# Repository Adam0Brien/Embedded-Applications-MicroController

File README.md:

# Embedded-Applications-MicroController
Microcontroller project for 2nd Year IoT &amp; WIT
---------------------------------------------------

<p1>Hello World working on the lcd Screen</p1>

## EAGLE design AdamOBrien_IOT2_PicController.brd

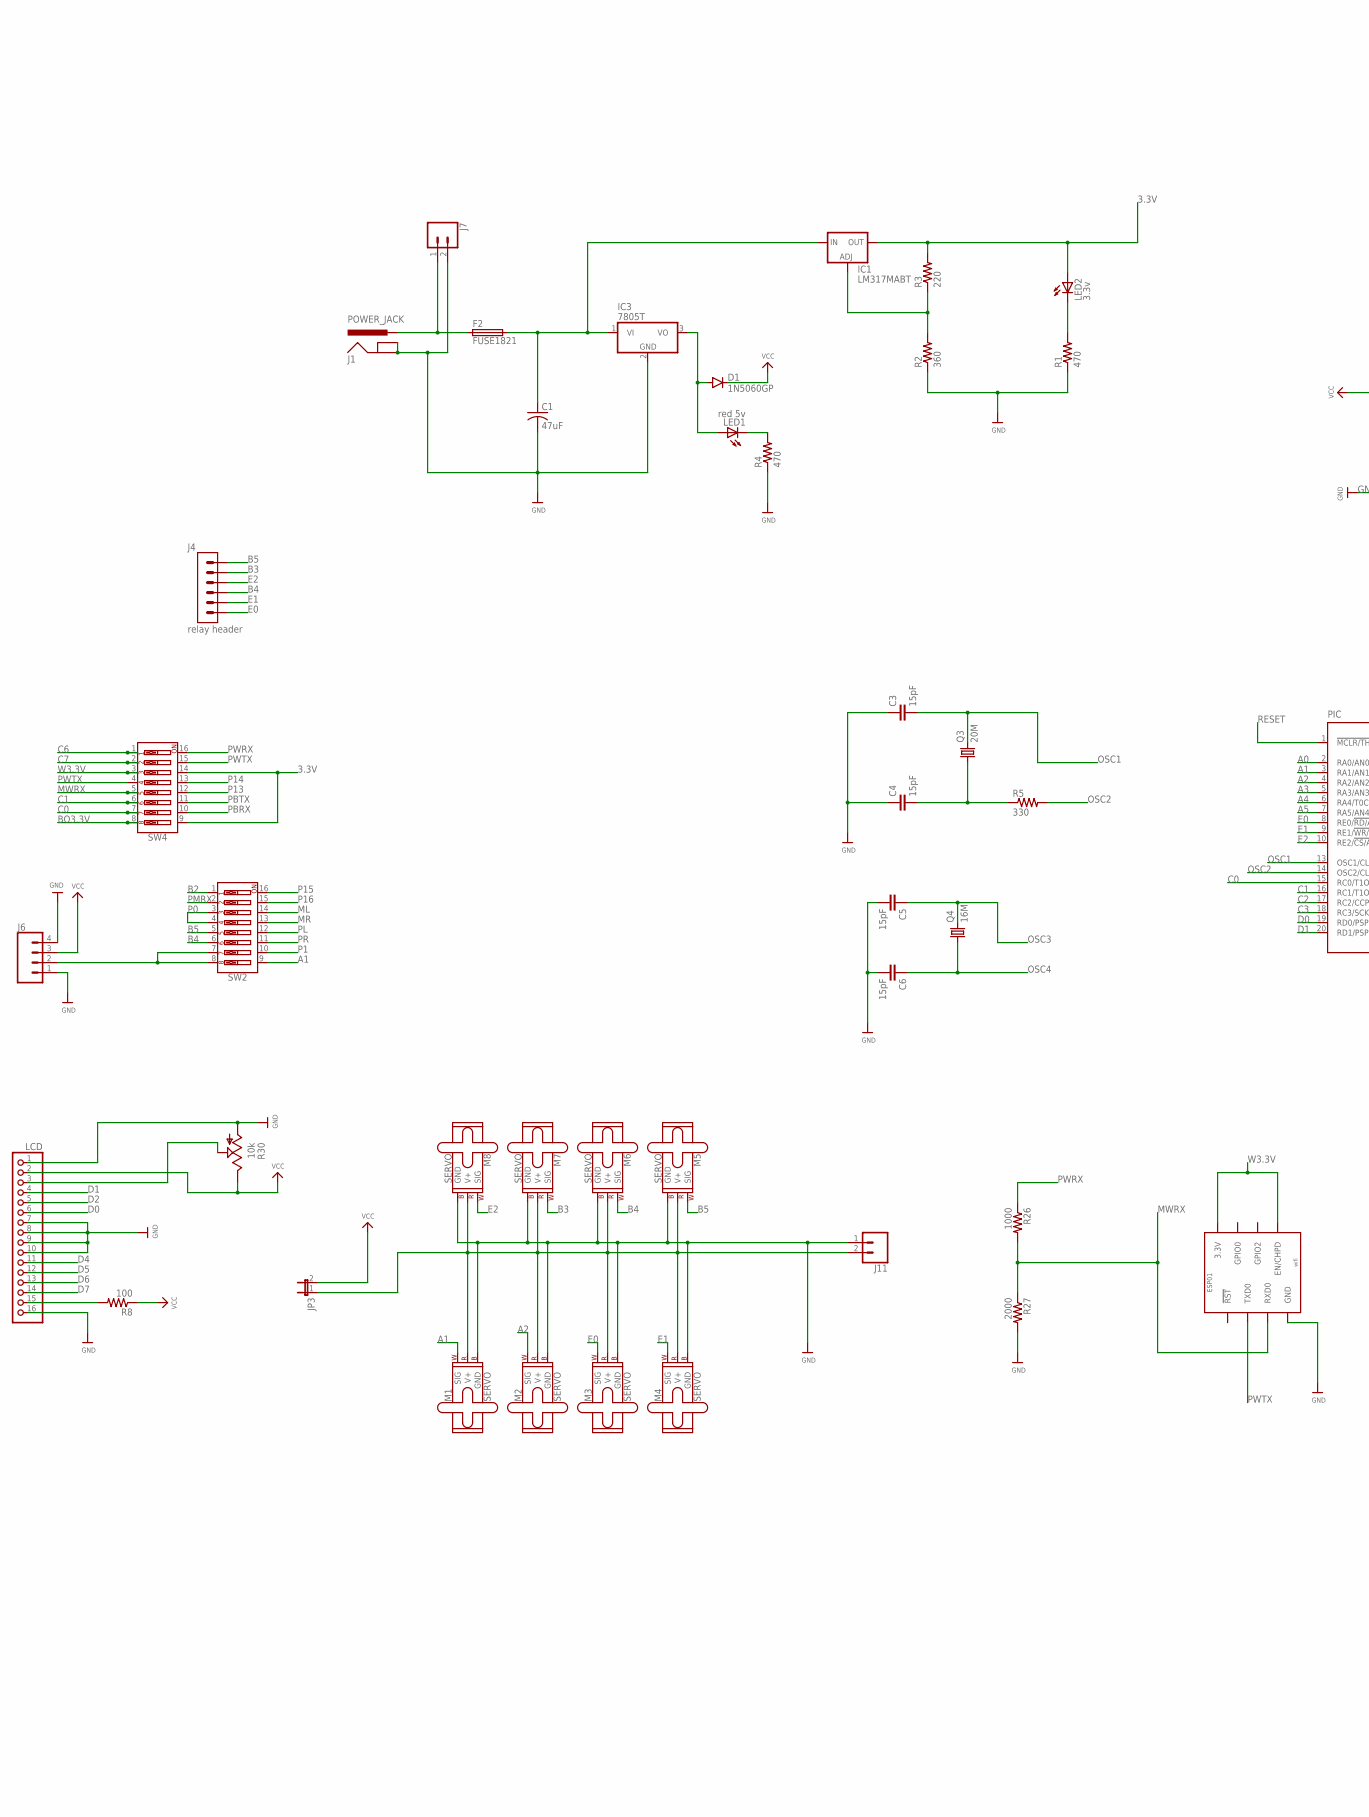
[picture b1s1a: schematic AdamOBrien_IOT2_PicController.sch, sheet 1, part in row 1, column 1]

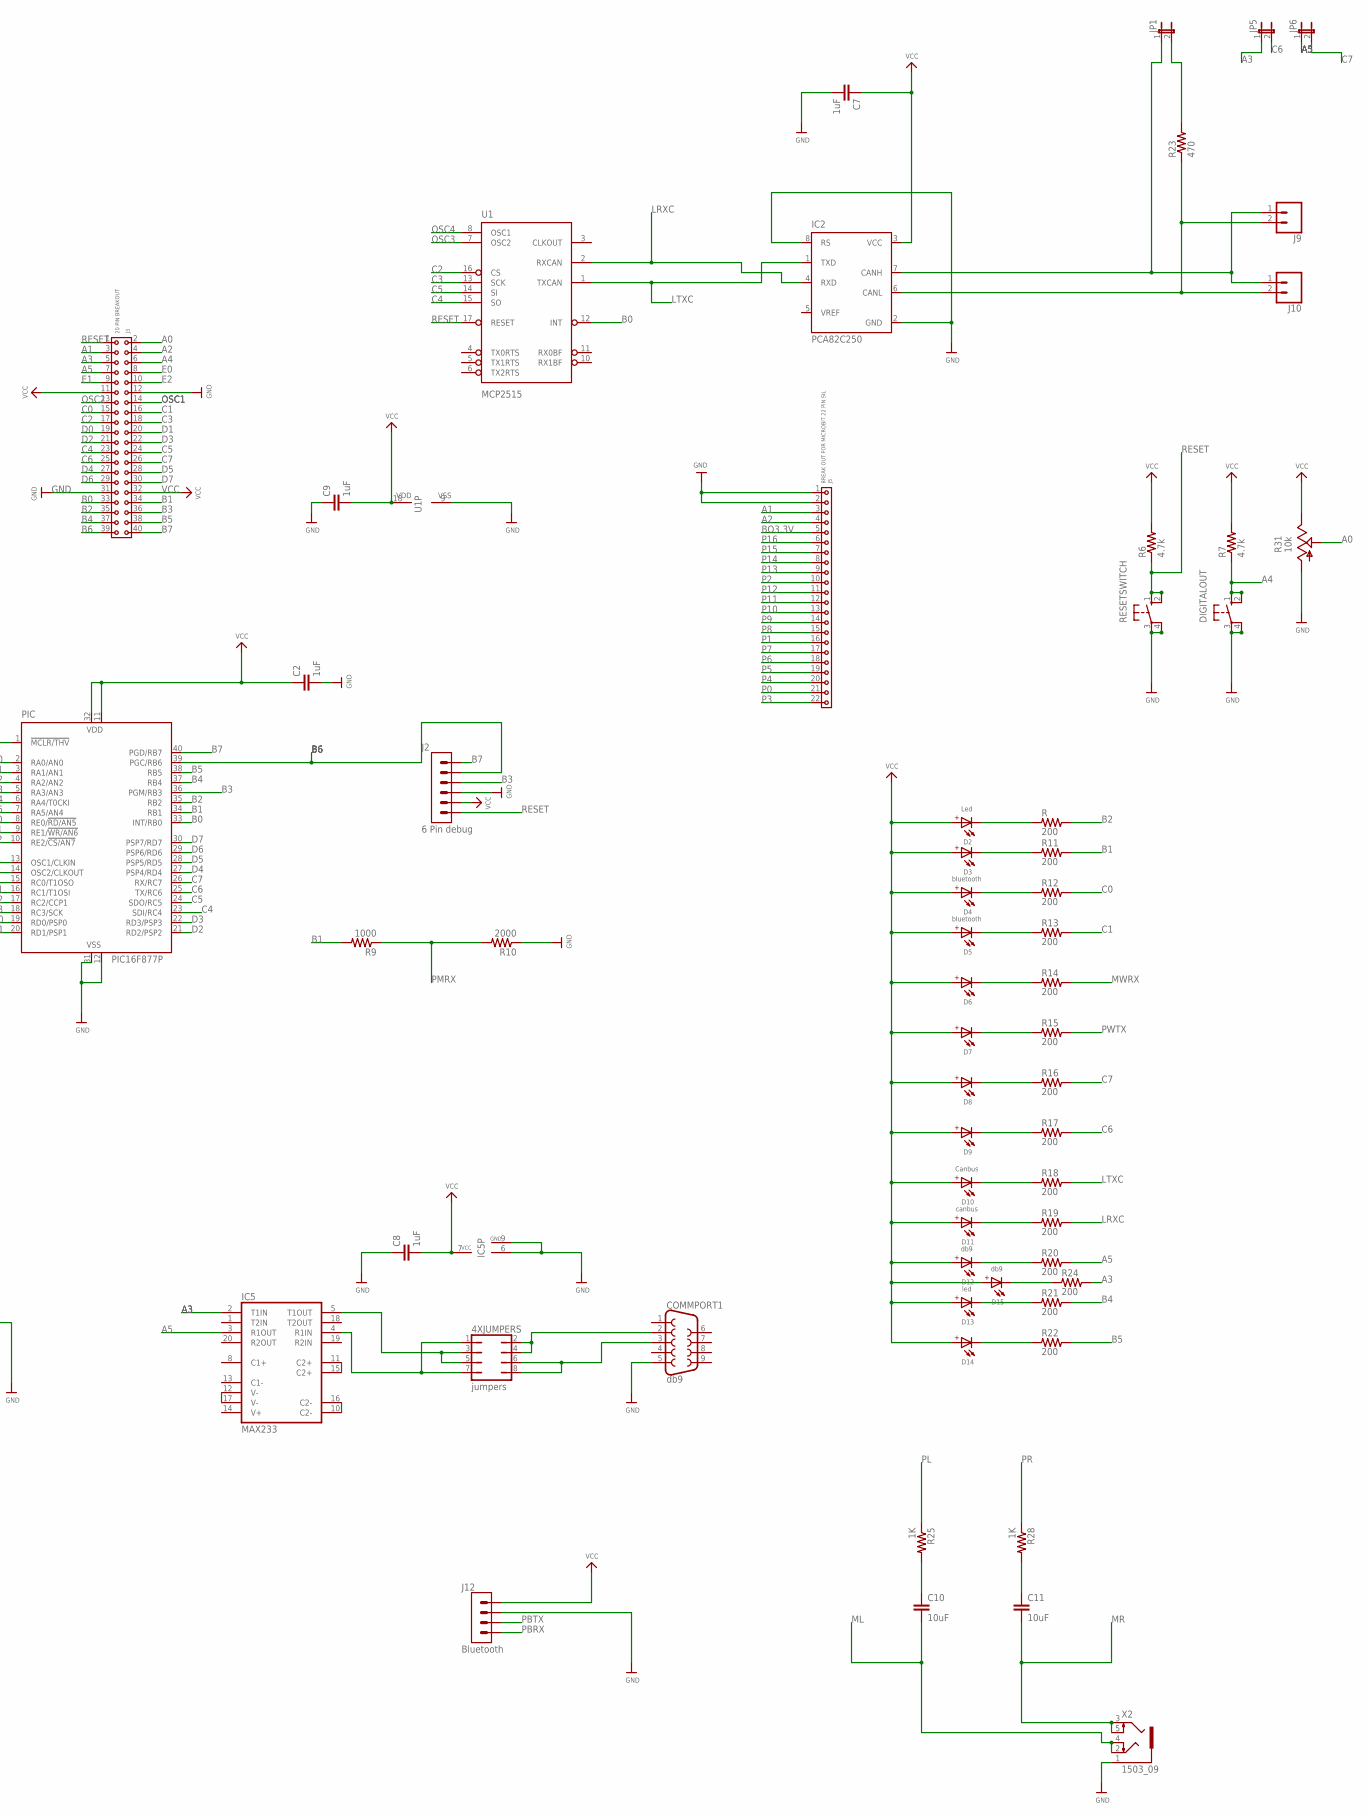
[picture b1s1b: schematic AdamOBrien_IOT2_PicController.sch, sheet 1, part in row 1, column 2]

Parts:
4XJUMPERS: jumpers; JP4Q
C1: 47uF; C025-024X044
C2, C7, C8, C9: 1uF; C2.5-2
C3, C4, C5, C6: 15pF; C2.5-2
C10, C11: 10uF; C2.5-2
COMMPORT1: db9; DB9
D1: 1N5060GP; DO15-12
D2: Led; WL-SITW_3528
D3, D6, D7, D8, D9, D14: WL-SITW_3528_15414185BA210; WL-SITW_3528
D4, D5: bluetooth; WL-SITW_3528
D10: Canbus; WL-SITW_3528
D11: canbus; WL-SITW_3528
D12, D15: db9; WL-SITW_3528
D13: led; WL-SITW_3528
DIGITALOUT: 10-XX; B3F-10XX
ESP01: wifi; ESP8266_ESP-01_NO-SILKSCREEN
F2: FUSE1821; FUSE_HOLDER_MENTOR-1821
IC1: LM317MABT; TO220L1
IC2: PCA82C250; DIL08
IC3: 7805T; TO220H
IC5: MAX233; DIL20
J1: POWER_JACK; POWER_JACK_PTH
J2: 6 Pin debug; 62000611121
J3: 20 PIN BREAKOUT; 61304021821
J4: relay header; 62000611121
J5: BREAK OUT FOR MICROBIT 22 PIN SIL; 61302211821
J6: CONN_04; 1X04
J7, J9, J10, J11: CONN_025MM; SCREWTERMINAL-5MM-2
J12: Bluetooth; 62000411121
JP1, JP3, JP5, JP6: JP1E; JP1
LCD: PINHD-1X16; 1X16
LED1: red 5v; LED5MM
LED2: 3.3v; LED5MM
M1, M2, M3, M4, M5, M6, M7, M8: SERVO; 1X03
PIC: PIC16F877P; DIL40
Q3: 20M; HC49/S
Q4: 16M; HC49/S
R, R11, R12, R13, R14, R15, R16, R17, R18, R19, R20, R21, R22, R24: 200; RC-MASTER-SMD_R1206MP
R1, R4, R23: 470; 0204/7
R2: 360; 0204/7
R3: 220; 0204/7
R5: 330; 0204/7
R6, R7: 4.7k; 0204/7
R8: 100; 0204/7
R9, R26: 1000; 0204/7
R10, R27: 2000; 0204/7
R25, R28: 1K; 0204/7
R30, R31: 10k; RS3
RESETSWITCH: 10-XX; B3F-10XX
SW2, SW4: DIP-08-PTH; DIPSWITCH-08
U1: MCP2515; DIP18
X2: 1503_09

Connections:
3.3V: IC1.2 (OUT), LED2.A, R3.2, SW4.9, SW4.14
A0: J3.2, PIC.2 (RA0/AN0), R31.S
A1: J3.3, J5.3, M1.1 (SIG), PIC.3 (RA1/AN1), SW2.9
A2: J3.4, J5.4, M2.1 (SIG), PIC.4 (RA2/AN2)
A3: IC5.2 (T1IN), J3.5, JP5.1, PIC.5 (RA3/AN3), R24.2
A4: DIGITALOUT.1 (S), DIGITALOUT.2 (S1), J3.6, PIC.6 (RA4/T0CKI), R7.1
A5: IC5.3 (R1OUT), J3.7, JP6.1, PIC.7 (RA5/AN4), R20.2
B0: J3.33, PIC.33 (INT/RB0), U1.12 (INT)
B1: J3.34, PIC.34 (RB1), R9.2, R11.2
B2: J3.35, PIC.35 (RB2), R.2, SW2.1
B3: J2.3, J3.36, J4.2, M7.1 (SIG), PIC.36 (PGM/RB3)
B4: J3.37, J4.4, M6.1 (SIG), PIC.37 (RB4), R21.2, SW2.6
B5: J3.38, J4.1, M5.1 (SIG), PIC.38 (RB5), R22.2, SW2.5
B6: J2.2, J3.39, PIC.39 (PGC/RB6)
B7: J2.1, J3.40, PIC.40 (PGD/RB7)
BO3.3V: J5.5, SW4.8
C0: J3.15, PIC.15 (RC0/T1OSO), R12.2, SW4.7
C1: J3.16, PIC.16 (RC1/T1OSI), R13.2, SW4.6
C2: J3.17, PIC.17 (RC2/CCP1), U1.16 (CS)
C3: J3.18, PIC.18 (RC3/SCK), U1.13 (SCK)
C4: J3.23, PIC.23 (SDI/RC4), U1.15 (SO)
C5: J3.24, PIC.24 (SDO/RC5), U1.14 (SI)
C6: J3.25, JP5.2, PIC.25 (TX/RC6), R17.2, SW4.1
C7: J3.26, JP6.2, PIC.26 (RX/RC7), R16.2, SW4.2
D0: J3.19, LCD.6, PIC.19 (RD0/PSP0)
D1: J3.20, LCD.4, PIC.20 (RD1/PSP1)
D2: J3.21, LCD.5, PIC.21 (RD2/PSP2)
D3: J3.22, PIC.22 (RD3/PSP3)
D4: J3.27, LCD.11, PIC.27 (PSP4/RD4)
D5: J3.28, LCD.12, PIC.28 (PSP5/RD5)
D6: J3.29, LCD.13, PIC.29 (PSP6/RD6)
D7: J3.30, LCD.14, PIC.30 (PSP7/RD7)
E0: J3.8, J4.6, M3.1 (SIG), PIC.8 (RE0/!RD/AN5)
E1: J3.9, J4.5, M4.1 (SIG), PIC.9 (RE1/!WR/AN6)
E2: J3.10, J4.3, M8.1 (SIG), PIC.10 (RE2/!CS/AN7)
GND: C1.2, C2.2, C3.1, C4.1, C5.2, C6.2, C7.2, C8.1, C9.1, COMMPORT1.5, DIGITALOUT.3, DIGITALOUT.4 (P1), ESP01.GND, IC2.2 (GND), IC2.8 (RS), IC3.2 (GND), IC5.6 (GND), IC5.9 (GND), J1.GND, J1.GNDBREAK, J2.4, J3.12, J3.31, J5.1, J5.2, J6.1, J6.4, J7.2, J11.1, J12.2, LCD.1, LCD.7, LCD.8, LCD.9, LCD.10, LCD.16, M1.3 (GND), M2.3 (GND), M3.3 (GND), M4.3 (GND), M5.3 (GND), M6.3 (GND), M7.3 (GND), M8.3 (GND), PIC.12 (VSS), PIC.31 (VSS), R1.1, R2.1, R4.1, R10.1, R27.2, R30.A, R31.A, RESETSWITCH.3, RESETSWITCH.4 (P1), U1.9 (VSS), X2.1
LRXC: IC2.4 (RXD), R19.2, U1.2 (RXCAN)
LTXC: IC2.1 (TXD), R18.2, U1.1 (TXCAN)
ML: C10.2, SW2.14, X2.2, X2.4
MR: C11.2, SW2.13, X2.3, X2.5
MWRX: ESP01.RX (RXD0), R14.2, R26.2, R27.1, SW4.5
unnamed: F2.A (1), J1.PWR, J7.1
unnamed: C1.1, F2.B (2), IC1.3 (IN), IC3.1 (VI)
unnamed: LED1.K (C), R4.2
unnamed: J6.2, SW2.7, SW2.8
unnamed: LED2.K (C), R1.2
unnamed: D1.A, IC3.3 (VO), LED1.A
unnamed: IC1.1 (ADJ), R2.2, R3.1
unnamed: C4.2, Q3.1, R5.1
unnamed: IC2.7 (CANH), J9.1, J10.1, JP1.1
unnamed: D2.2 (-), R.1
unnamed: D3.2 (-), R11.1
unnamed: JP1.2, R23.2
unnamed: D4.2 (-), R12.1
unnamed: LCD.3, R30.S
unnamed: D5.2 (-), R13.1
unnamed: LCD.15, R8.2
unnamed: D15.2 (-), R24.1
unnamed: D6.2 (-), R14.1
unnamed: D7.2 (-), R15.1
unnamed: D8.2 (-), R16.1
unnamed: C10.1, R25.2
unnamed: D9.2 (-), R17.1
unnamed: D10.2 (-), R18.1
unnamed: D11.2 (-), R19.1
unnamed: D12.2 (-), R20.1
unnamed: D13.2 (-), R21.1
unnamed: D14.2 (-), R22.1
unnamed: IC2.6 (CANL), J9.2, J10.2, R23.1
unnamed: 4XJUMPERS.6, 4XJUMPERS.8, COMMPORT1.3
unnamed: 4XJUMPERS.2, 4XJUMPERS.4, COMMPORT1.2
unnamed: 4XJUMPERS.3, 4XJUMPERS.5, IC5.5 (T1OUT)
unnamed: J11.2, JP3.1, M1.2 (V+), M2.2 (V+), M3.2 (V+), M4.2 (V+), M5.2 (V+), M6.2 (V+), M7.2 (V+), M8.2 (V+)
unnamed: 4XJUMPERS.1, 4XJUMPERS.7, IC5.4 (R1IN)
unnamed: IC5.11 (C2+), IC5.15 (C2+)
unnamed: IC5.10 (C2-), IC5.16 (C2-)
unnamed: IC5.12 (V-), IC5.17 (V-)
unnamed: C11.1, R28.2
OSC1: C3.2, J3.14, PIC.13 (OSC1/CLKIN), Q3.2
OSC2: J3.13, PIC.14 (OSC2/CLKOUT), R5.2
OSC3: C5.1, Q4.2, U1.7 (OSC2)
OSC4: C6.1, Q4.1, U1.8 (OSC1)
P0: J5.21, SW2.3, SW2.4
P1: J5.16, SW2.10
P2: J5.10
P3: J5.22
P4: J5.20
P5: J5.19
P6: J5.18
P7: J5.17
P8: J5.15
P9: J5.14
P10: J5.13
P11: J5.12
P12: J5.11
P13: J5.9, SW4.12
P14: J5.8, SW4.13
P15: J5.7, SW2.16
P16: J5.6, SW2.15
PBRX: J12.4, SW4.10
PBTX: J12.3, SW4.11
PL: R25.1, SW2.12
PMRX: R9.1, R10.2, SW2.2
PR: R28.1, SW2.11
PWRX: R26.1, SW4.16
PWTX: ESP01.TX (TXD0), R15.2, SW4.4, SW4.15
RESET: J2.6, J3.1, PIC.1 (!MCLR/THV), R6.1, RESETSWITCH.1 (S), RESETSWITCH.2 (S1), U1.17 (RESET)
VCC: C2.1, C7.1, C8.2, C9.2, D1.C, D2.1 (+), D3.1 (+), D4.1 (+), D5.1 (+), D6.1 (+), D7.1 (+), D8.1 (+), D9.1 (+), D10.1 (+), D11.1 (+), D12.1 (+), D13.1 (+), D14.1 (+), D15.1 (+), IC2.3 (VCC), IC5.7 (VCC), J2.5, J3.11, J3.32, J6.3, J12.1, JP3.2, LCD.2, PIC.11 (VDD), PIC.32 (VDD), R6.2, R7.2, R8.1, R30.E, R31.E, U1.18 (VDD)
W3.3V: ESP01.3V3 (3.3V), ESP01.EN/CH_PD (EN/CHPD), SW4.3

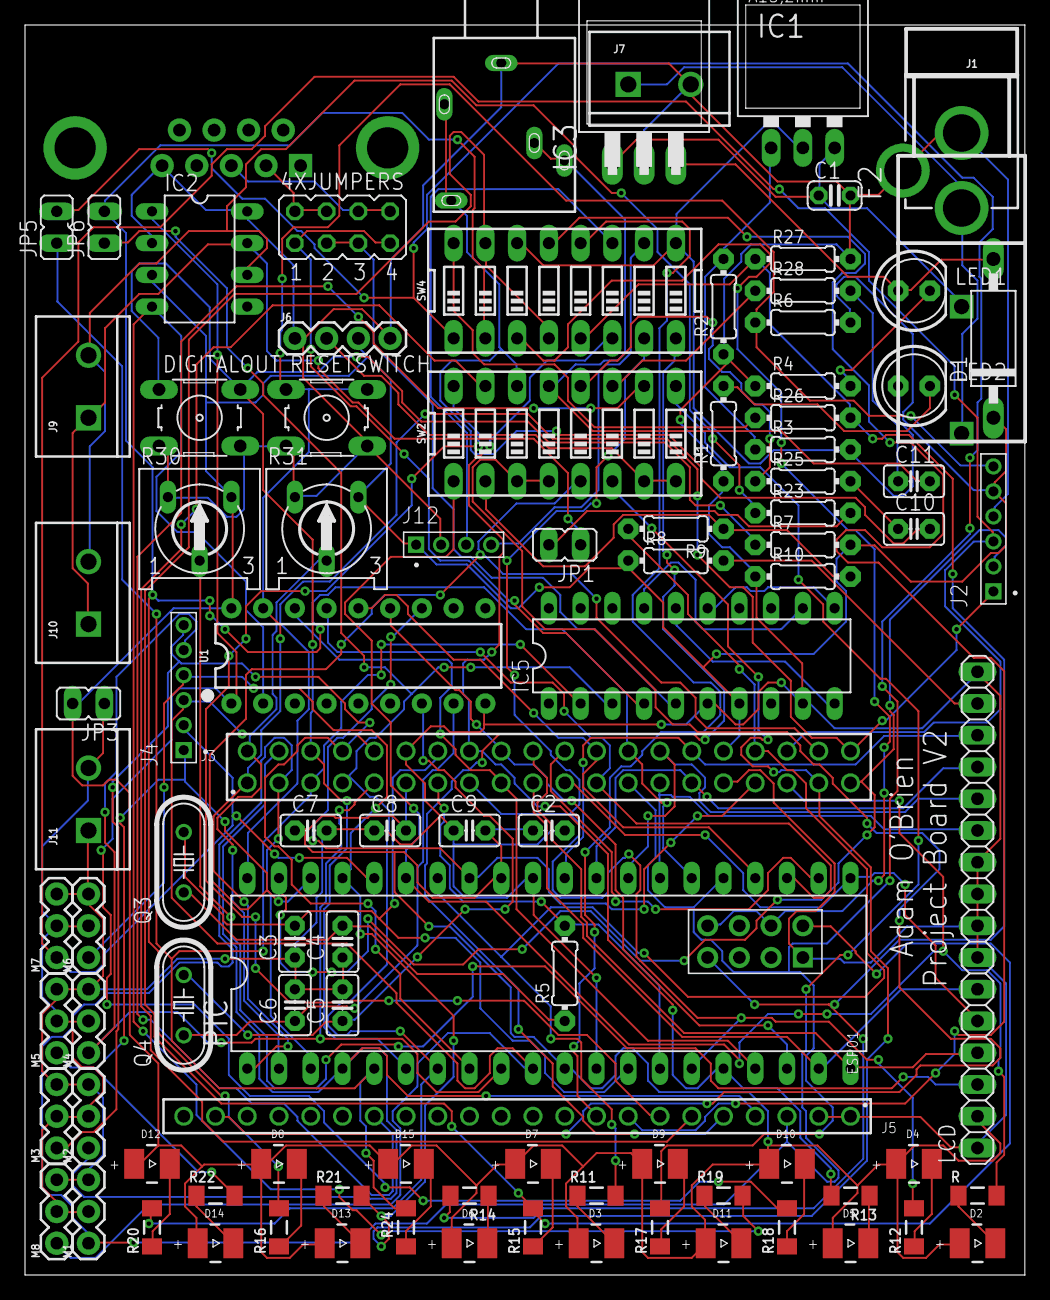
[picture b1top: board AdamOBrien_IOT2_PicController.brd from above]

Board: 2 copper layers, 80.0 x 100.0 mm, 100 parts (1 on the bottom side), 98 nets.

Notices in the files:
parts and their libraries:
Wurth_Infrared_WL-SITW: Copyright: Würth Elektronik
SparkFun-Connectors: Licensing: Creative Commons ShareAlike 4.0 International - https://creativecommons.org/licenses/by-sa/4.0
